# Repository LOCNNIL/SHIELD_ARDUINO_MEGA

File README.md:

# SHIELD_ARDUINO_MEGA
An Arduino Mega Shield with the purpose to be a Flight controller

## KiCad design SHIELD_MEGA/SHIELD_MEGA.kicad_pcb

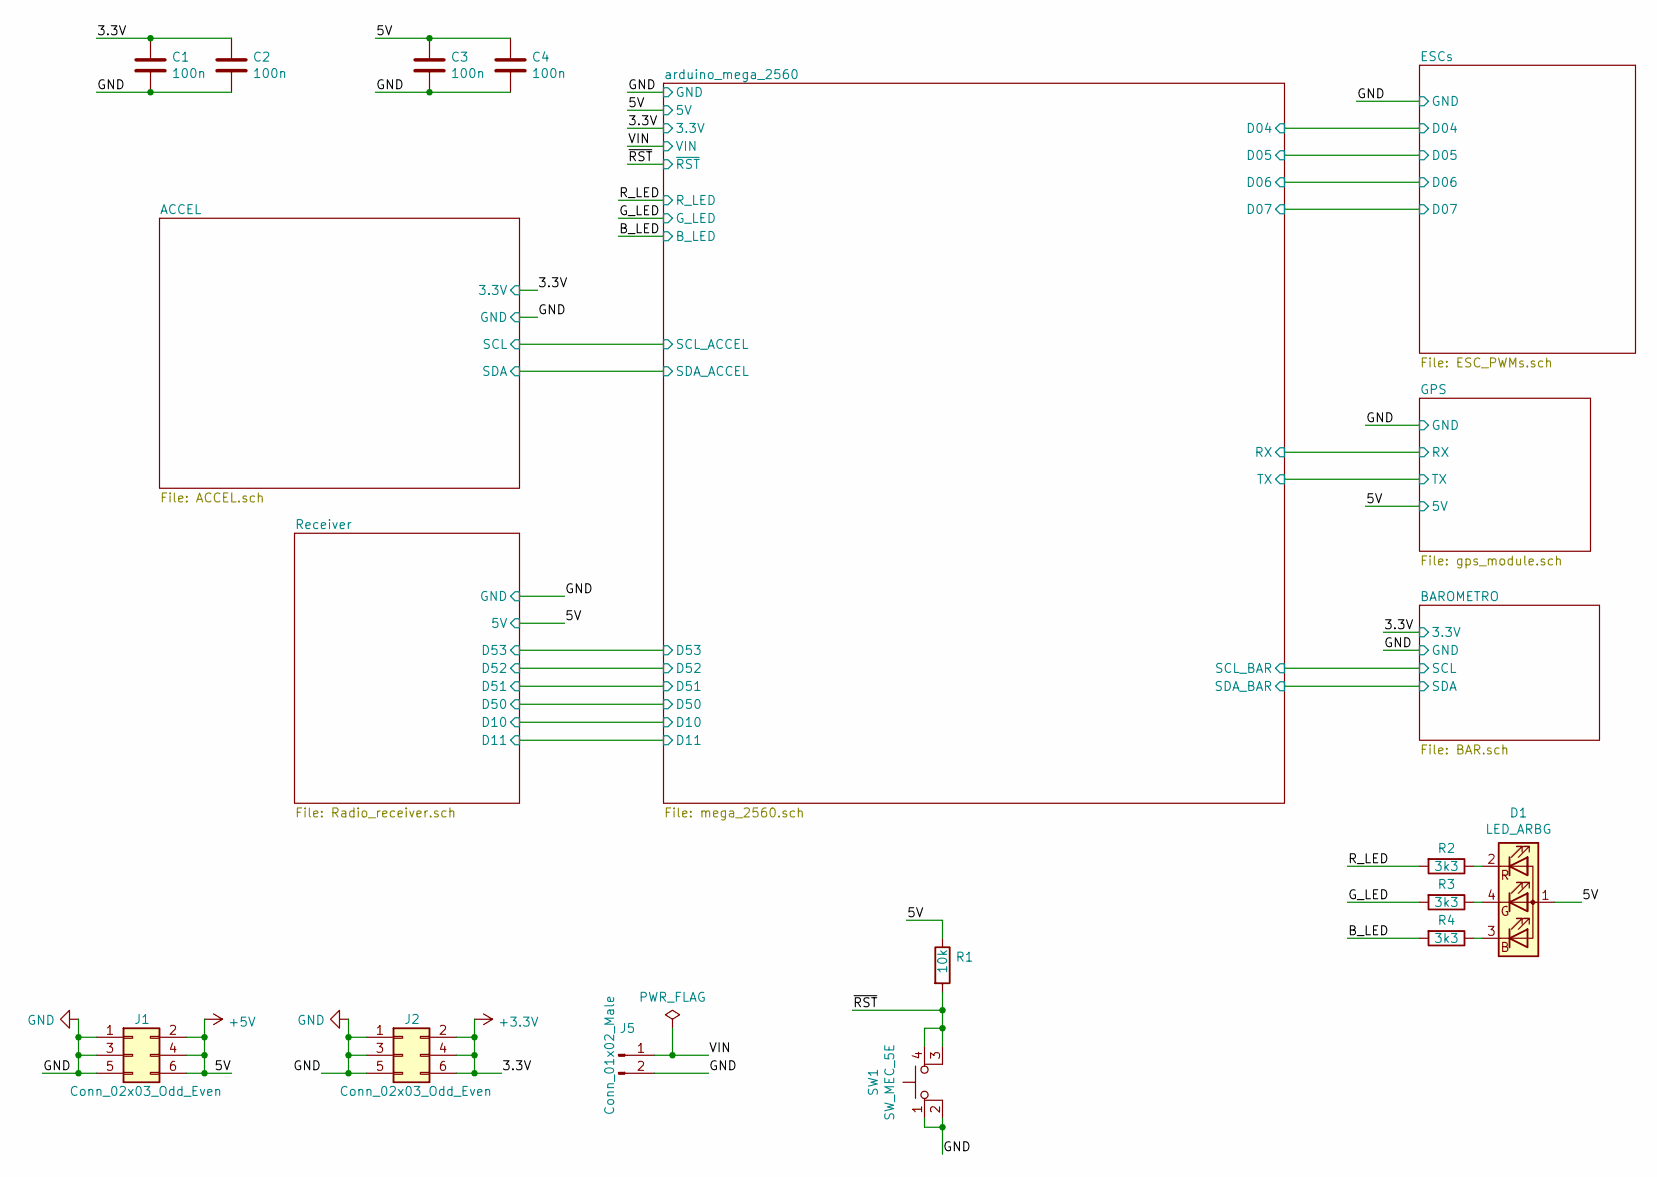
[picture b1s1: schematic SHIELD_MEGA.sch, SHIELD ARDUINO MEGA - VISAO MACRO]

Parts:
C1, C2, C3, C4: 100n; C_0805_2012Metric_Pad1.18x1.45mm_HandSolder
D1: LED_ARBG; LED_LL-R3528RGBC-008-B
J1, J2: Conn_02x03_Odd_Even; PinHeader_2x03_P2.54mm_Vertical
J5: Conn_01x02_Male; PinHeader_1x02_P2.54mm_Vertical
R1: 10k; R_0805_2012Metric_Pad1.20x1.40mm_HandSolder
R2, R3, R4: 3k3; R_0805_2012Metric_Pad1.20x1.40mm_HandSolder
SW1: SW_MEC_5E; TE_1825910-2

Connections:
+3V3: C1.1, C2.1, J2.2, J2.4, J2.6; also elsewhere on the board
+5V: C3.1, C4.1, D1.1 (A), J1.2, J1.4, J1.6, R1.1; also elsewhere on the board
/B_LED: R4.2; also elsewhere on the board
/G_LED: R3.2; also elsewhere on the board
/R_LED: R2.2; also elsewhere on the board
/VIN: J5.1; also elsewhere on the board
/~RST: R1.2, SW1.3 (K), SW1.4 (A); also elsewhere on the board
GND: C1.2, C2.2, C3.2, C4.2, J1.1, J1.3, J1.5, J2.1, J2.3, J2.5, J5.2, SW1.1, SW1.2; also elsewhere on the board
unnamed: D1.2 (RK), R2.1
unnamed: D1.3 (BK), R4.1
unnamed: D1.4 (GK), R3.1

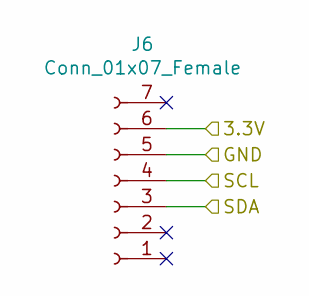
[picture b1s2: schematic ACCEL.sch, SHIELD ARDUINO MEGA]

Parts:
J6: Conn_01x07_Female; PinSocket_1x07_P2.54mm_Vertical

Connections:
+3V3: J6.6; also elsewhere on the board
/ACCEL/SCL: J6.4; also elsewhere on the board
/ACCEL/SDA: J6.3; also elsewhere on the board
GND: J6.5; also elsewhere on the board

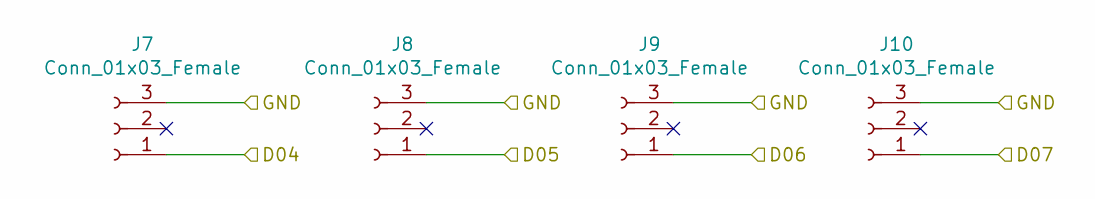
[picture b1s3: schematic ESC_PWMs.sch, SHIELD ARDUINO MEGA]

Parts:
J7, J8, J9, J10: Conn_01x03_Female; PinSocket_1x03_P2.54mm_Vertical

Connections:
/ESCs/D04: J7.1; also elsewhere on the board
/ESCs/D05: J8.1; also elsewhere on the board
/ESCs/D06: J9.1; also elsewhere on the board
/ESCs/D07: J10.1; also elsewhere on the board
GND: J7.3, J8.3, J9.3, J10.3; also elsewhere on the board

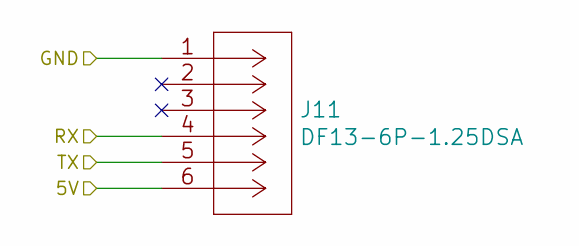
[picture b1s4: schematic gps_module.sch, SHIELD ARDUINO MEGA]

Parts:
J11: DF13-6P-1.25DSA; Hirose_DF13-06P-1.25DSA_1x06_P1.25mm_Vertical

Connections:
+5V: J11.6; also elsewhere on the board
/GPS/RX: J11.4; also elsewhere on the board
/GPS/TX: J11.5; also elsewhere on the board
GND: J11.1; also elsewhere on the board

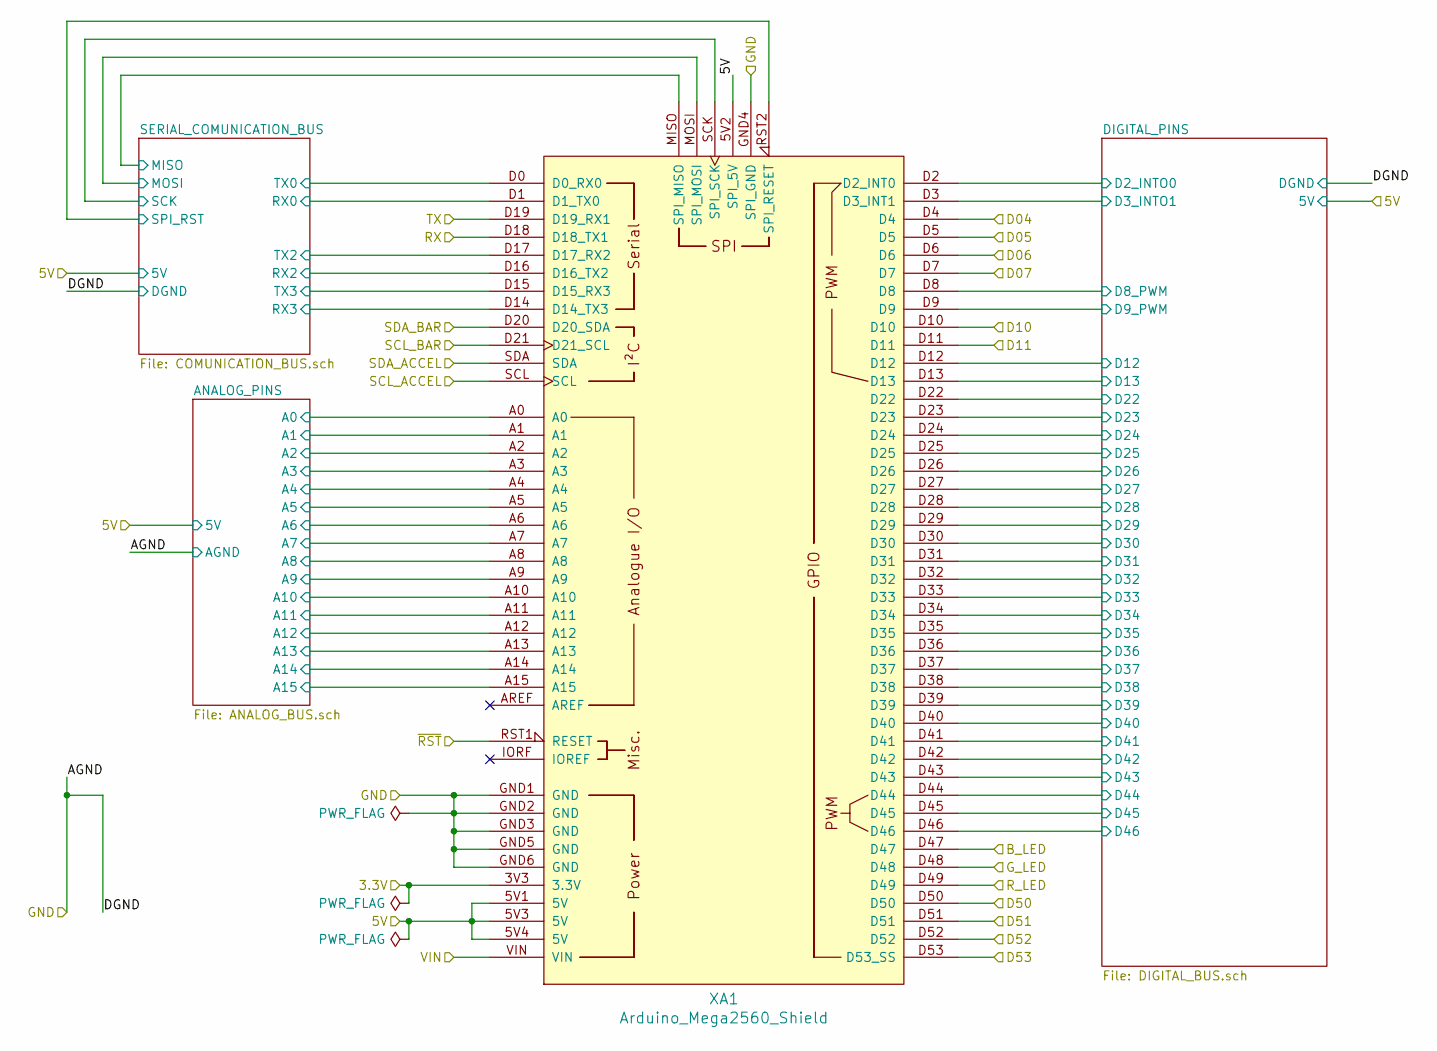
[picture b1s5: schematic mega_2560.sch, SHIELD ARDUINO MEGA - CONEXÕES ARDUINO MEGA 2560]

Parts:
XA1: Arduino_Mega2560_Shield

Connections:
+3V3: XA1.3V3 (3.3V); also elsewhere on the board
+5V: XA1.5V1 (5V), XA1.5V2 (SPI_5V), XA1.5V3 (5V), XA1.5V4 (5V); also elsewhere on the board
/ACCEL/SCL: XA1.SCL; also elsewhere on the board
/ACCEL/SDA: XA1.SDA; also elsewhere on the board
/BAROMETRO/SCL: XA1.D21 (D21_SCL); also elsewhere on the board
/BAROMETRO/SDA: XA1.D20 (D20_SDA); also elsewhere on the board
/B_LED: XA1.D47; also elsewhere on the board
/ESCs/D04: XA1.D4; also elsewhere on the board
/ESCs/D05: XA1.D5; also elsewhere on the board
/ESCs/D06: XA1.D6; also elsewhere on the board
/ESCs/D07: XA1.D7; also elsewhere on the board
/GPS/RX: XA1.D18 (D18_TX1); also elsewhere on the board
/GPS/TX: XA1.D19 (D19_RX1); also elsewhere on the board
/G_LED: XA1.D48; also elsewhere on the board
/R_LED: XA1.D49; also elsewhere on the board
/Receiver/D10: XA1.D10; also elsewhere on the board
/Receiver/D11: XA1.D11; also elsewhere on the board
/Receiver/D50: XA1.D50; also elsewhere on the board
/Receiver/D51: XA1.D51; also elsewhere on the board
/Receiver/D52: XA1.D52; also elsewhere on the board
/Receiver/D53: XA1.D53 (D53_SS); also elsewhere on the board
/VIN: XA1.VIN; also elsewhere on the board
/arduino_mega_2560/ANALOG_PINS/A0: XA1.A0; also elsewhere on the board
/arduino_mega_2560/ANALOG_PINS/A1: XA1.A1; also elsewhere on the board
/arduino_mega_2560/ANALOG_PINS/A2: XA1.A2; also elsewhere on the board
/arduino_mega_2560/ANALOG_PINS/A3: XA1.A3; also elsewhere on the board
/arduino_mega_2560/ANALOG_PINS/A4: XA1.A4; also elsewhere on the board
/arduino_mega_2560/ANALOG_PINS/A5: XA1.A5; also elsewhere on the board
/arduino_mega_2560/ANALOG_PINS/A6: XA1.A6; also elsewhere on the board
/arduino_mega_2560/ANALOG_PINS/A7: XA1.A7; also elsewhere on the board
/arduino_mega_2560/ANALOG_PINS/A8: XA1.A8; also elsewhere on the board
/arduino_mega_2560/ANALOG_PINS/A9: XA1.A9; also elsewhere on the board
/arduino_mega_2560/ANALOG_PINS/A10: XA1.A10; also elsewhere on the board
/arduino_mega_2560/ANALOG_PINS/A11: XA1.A11; also elsewhere on the board
/arduino_mega_2560/ANALOG_PINS/A12: XA1.A12; also elsewhere on the board
/arduino_mega_2560/ANALOG_PINS/A13: XA1.A13; also elsewhere on the board
/arduino_mega_2560/ANALOG_PINS/A14: XA1.A14; also elsewhere on the board
/arduino_mega_2560/ANALOG_PINS/A15: XA1.A15; also elsewhere on the board
/arduino_mega_2560/DIGITAL_PINS/D2_INTO0: XA1.D2 (D2_INT0); also elsewhere on the board
/arduino_mega_2560/DIGITAL_PINS/D3_INTO1: XA1.D3 (D3_INT1); also elsewhere on the board
/arduino_mega_2560/DIGITAL_PINS/D8_PWM: XA1.D8; also elsewhere on the board
/arduino_mega_2560/DIGITAL_PINS/D9_PWM: XA1.D9; also elsewhere on the board
/arduino_mega_2560/DIGITAL_PINS/D12: XA1.D12; also elsewhere on the board
/arduino_mega_2560/DIGITAL_PINS/D13: XA1.D13; also elsewhere on the board
/arduino_mega_2560/DIGITAL_PINS/D22: XA1.D22; also elsewhere on the board
/arduino_mega_2560/DIGITAL_PINS/D23: XA1.D23; also elsewhere on the board
/arduino_mega_2560/DIGITAL_PINS/D24: XA1.D24; also elsewhere on the board
/arduino_mega_2560/DIGITAL_PINS/D25: XA1.D25; also elsewhere on the board
/arduino_mega_2560/DIGITAL_PINS/D26: XA1.D26; also elsewhere on the board
/arduino_mega_2560/DIGITAL_PINS/D27: XA1.D27; also elsewhere on the board
/arduino_mega_2560/DIGITAL_PINS/D28: XA1.D28; also elsewhere on the board
/arduino_mega_2560/DIGITAL_PINS/D29: XA1.D29; also elsewhere on the board
/arduino_mega_2560/DIGITAL_PINS/D30: XA1.D30; also elsewhere on the board
/arduino_mega_2560/DIGITAL_PINS/D31: XA1.D31; also elsewhere on the board
/arduino_mega_2560/DIGITAL_PINS/D32: XA1.D32; also elsewhere on the board
/arduino_mega_2560/DIGITAL_PINS/D33: XA1.D33; also elsewhere on the board
/arduino_mega_2560/DIGITAL_PINS/D34: XA1.D34; also elsewhere on the board
/arduino_mega_2560/DIGITAL_PINS/D35: XA1.D35; also elsewhere on the board
/arduino_mega_2560/DIGITAL_PINS/D36: XA1.D36; also elsewhere on the board
/arduino_mega_2560/DIGITAL_PINS/D37: XA1.D37; also elsewhere on the board
/arduino_mega_2560/DIGITAL_PINS/D38: XA1.D38; also elsewhere on the board
/arduino_mega_2560/DIGITAL_PINS/D39: XA1.D39; also elsewhere on the board
/arduino_mega_2560/DIGITAL_PINS/D40: XA1.D40; also elsewhere on the board
/arduino_mega_2560/DIGITAL_PINS/D41: XA1.D41; also elsewhere on the board
/arduino_mega_2560/DIGITAL_PINS/D42: XA1.D42; also elsewhere on the board
/arduino_mega_2560/DIGITAL_PINS/D43: XA1.D43; also elsewhere on the board
/arduino_mega_2560/DIGITAL_PINS/D44: XA1.D44; also elsewhere on the board
/arduino_mega_2560/DIGITAL_PINS/D45: XA1.D45; also elsewhere on the board
/arduino_mega_2560/DIGITAL_PINS/D46: XA1.D46; also elsewhere on the board
/arduino_mega_2560/SERIAL_COMUNICATION_BUS/MISO: XA1.MISO (SPI_MISO); also elsewhere on the board
/arduino_mega_2560/SERIAL_COMUNICATION_BUS/MOSI: XA1.MOSI (SPI_MOSI); also elsewhere on the board
/arduino_mega_2560/SERIAL_COMUNICATION_BUS/RX0: XA1.D1 (D1_TX0); also elsewhere on the board
/arduino_mega_2560/SERIAL_COMUNICATION_BUS/RX2: XA1.D16 (D16_TX2); also elsewhere on the board
/arduino_mega_2560/SERIAL_COMUNICATION_BUS/RX3: XA1.D14 (D14_TX3); also elsewhere on the board
/arduino_mega_2560/SERIAL_COMUNICATION_BUS/SCK: XA1.SCK (SPI_SCK); also elsewhere on the board
/arduino_mega_2560/SERIAL_COMUNICATION_BUS/SPI_RST: XA1.RST2 (SPI_RESET); also elsewhere on the board
/arduino_mega_2560/SERIAL_COMUNICATION_BUS/TX0: XA1.D0 (D0_RX0); also elsewhere on the board
/arduino_mega_2560/SERIAL_COMUNICATION_BUS/TX2: XA1.D17 (D17_RX2); also elsewhere on the board
/arduino_mega_2560/SERIAL_COMUNICATION_BUS/TX3: XA1.D15 (D15_RX3); also elsewhere on the board
/~RST: XA1.RST1 (RESET); also elsewhere on the board
GND: XA1.GND1 (GND), XA1.GND2 (GND), XA1.GND3 (GND), XA1.GND4 (SPI_GND), XA1.GND5 (GND), XA1.GND6 (GND); also elsewhere on the board

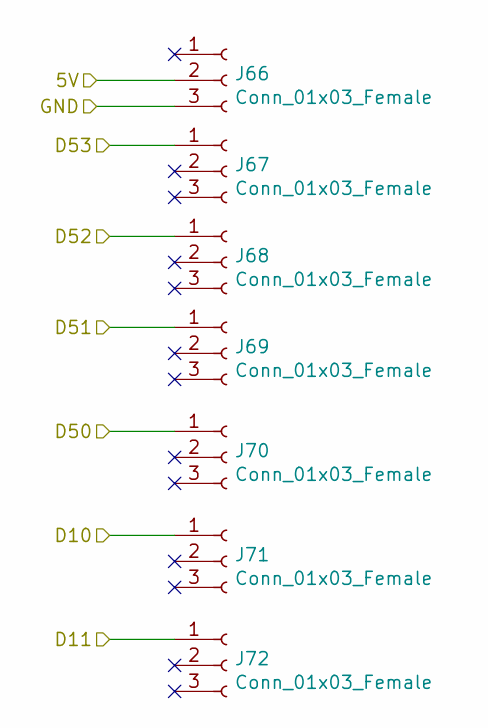
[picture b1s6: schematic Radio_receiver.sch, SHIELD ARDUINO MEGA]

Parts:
J66, J67, J68, J69, J70, J71, J72: Conn_01x03_Female; PinSocket_1x03_P2.54mm_Vertical

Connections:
+5V: J66.2; also elsewhere on the board
/Receiver/D10: J71.1; also elsewhere on the board
/Receiver/D11: J72.1; also elsewhere on the board
/Receiver/D50: J70.1; also elsewhere on the board
/Receiver/D51: J69.1; also elsewhere on the board
/Receiver/D52: J68.1; also elsewhere on the board
/Receiver/D53: J67.1; also elsewhere on the board
GND: J66.3; also elsewhere on the board

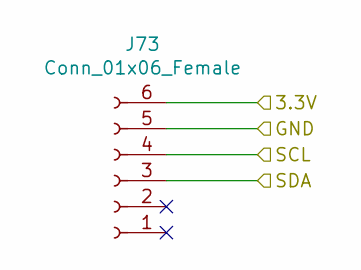
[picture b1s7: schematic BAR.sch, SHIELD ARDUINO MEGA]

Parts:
J73: Conn_01x06_Female; PinSocket_1x06_P2.54mm_Vertical

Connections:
+3V3: J73.6; also elsewhere on the board
/BAROMETRO/SCL: J73.4; also elsewhere on the board
/BAROMETRO/SDA: J73.3; also elsewhere on the board
GND: J73.5; also elsewhere on the board

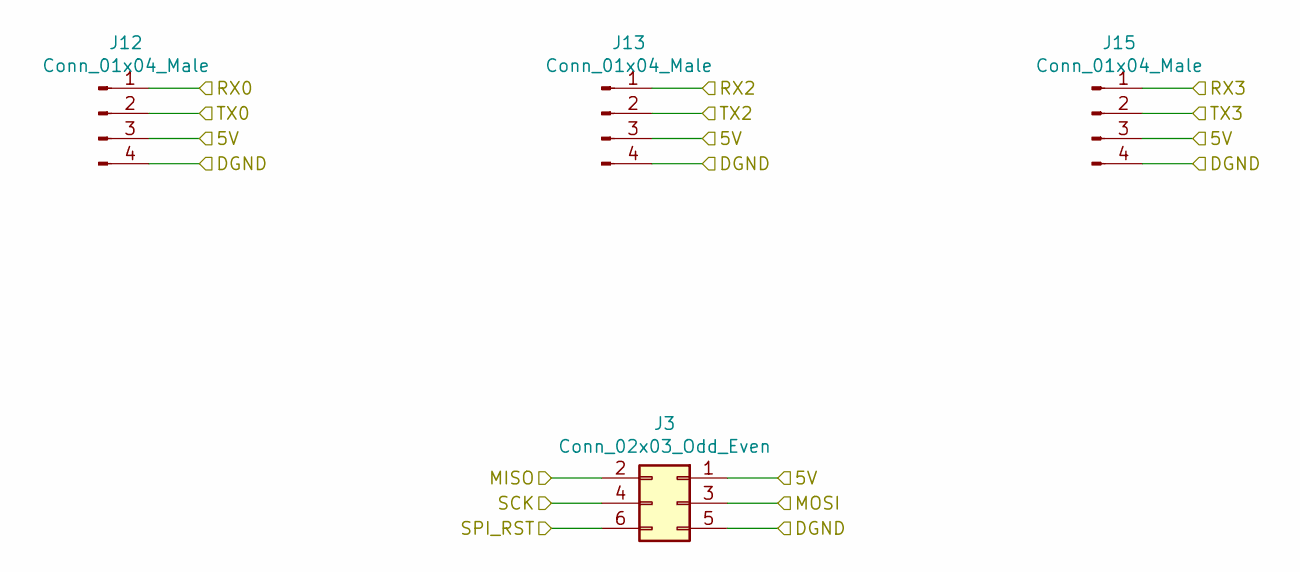
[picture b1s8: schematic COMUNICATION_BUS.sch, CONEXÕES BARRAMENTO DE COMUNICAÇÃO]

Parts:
J3: Conn_02x03_Odd_Even; PinSocket_2x03_P2.54mm_Vertical
J12, J13, J15: Conn_01x04_Male; PinHeader_1x04_P2.54mm_Vertical

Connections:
+5V: J3.1, J12.3, J13.3, J15.3; also elsewhere on the board
/arduino_mega_2560/SERIAL_COMUNICATION_BUS/MISO: J3.2; also elsewhere on the board
/arduino_mega_2560/SERIAL_COMUNICATION_BUS/MOSI: J3.3; also elsewhere on the board
/arduino_mega_2560/SERIAL_COMUNICATION_BUS/RX0: J12.1; also elsewhere on the board
/arduino_mega_2560/SERIAL_COMUNICATION_BUS/RX2: J13.1; also elsewhere on the board
/arduino_mega_2560/SERIAL_COMUNICATION_BUS/RX3: J15.1; also elsewhere on the board
/arduino_mega_2560/SERIAL_COMUNICATION_BUS/SCK: J3.4; also elsewhere on the board
/arduino_mega_2560/SERIAL_COMUNICATION_BUS/SPI_RST: J3.6; also elsewhere on the board
/arduino_mega_2560/SERIAL_COMUNICATION_BUS/TX0: J12.2; also elsewhere on the board
/arduino_mega_2560/SERIAL_COMUNICATION_BUS/TX2: J13.2; also elsewhere on the board
/arduino_mega_2560/SERIAL_COMUNICATION_BUS/TX3: J15.2; also elsewhere on the board
GND: J3.5, J12.4, J13.4, J15.4; also elsewhere on the board

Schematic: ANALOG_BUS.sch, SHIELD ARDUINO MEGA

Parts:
J16, J17, J18, J19, J20, J21, J22, J23, J24, J25, J26, J27, J28, J29, J30, J31: Conn_01x03_Male; PinHeader_1x03_P2.54mm_Vertical

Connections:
+5V: J16.2, J17.2, J18.2, J19.2, J20.2, J21.2, J22.2, J23.2, J24.2, J25.2, J26.2, J27.2, J28.2, J29.2, J30.2, J31.2; also elsewhere on the board
/arduino_mega_2560/ANALOG_PINS/A0: J16.1; also elsewhere on the board
/arduino_mega_2560/ANALOG_PINS/A1: J17.1; also elsewhere on the board
/arduino_mega_2560/ANALOG_PINS/A2: J18.1; also elsewhere on the board
/arduino_mega_2560/ANALOG_PINS/A3: J19.1; also elsewhere on the board
/arduino_mega_2560/ANALOG_PINS/A4: J20.1; also elsewhere on the board
/arduino_mega_2560/ANALOG_PINS/A5: J21.1; also elsewhere on the board
/arduino_mega_2560/ANALOG_PINS/A6: J22.1; also elsewhere on the board
/arduino_mega_2560/ANALOG_PINS/A7: J23.1; also elsewhere on the board
/arduino_mega_2560/ANALOG_PINS/A8: J24.1; also elsewhere on the board
/arduino_mega_2560/ANALOG_PINS/A9: J25.1; also elsewhere on the board
/arduino_mega_2560/ANALOG_PINS/A10: J26.1; also elsewhere on the board
/arduino_mega_2560/ANALOG_PINS/A11: J27.1; also elsewhere on the board
/arduino_mega_2560/ANALOG_PINS/A12: J28.1; also elsewhere on the board
/arduino_mega_2560/ANALOG_PINS/A13: J29.1; also elsewhere on the board
/arduino_mega_2560/ANALOG_PINS/A14: J30.1; also elsewhere on the board
/arduino_mega_2560/ANALOG_PINS/A15: J31.1; also elsewhere on the board
GND: J16.3, J17.3, J18.3, J19.3, J20.3, J21.3, J22.3, J23.3, J24.3, J25.3, J26.3, J27.3, J28.3, J29.3, J30.3, J31.3; also elsewhere on the board

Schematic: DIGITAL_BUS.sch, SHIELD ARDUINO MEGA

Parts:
J32, J33, J34, J35, J36, J37, J38, J39, J40, J41, J42, J43, J44, J45, J46, J47, J48, J49, J50, J51, J52, J53, J54, J55, J56, J57, J58, J62, J63, J64, J65: Conn_01x03_Male; PinHeader_1x03_P2.54mm_Vertical

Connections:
+5V: J32.2, J33.2, J34.2, J35.2, J36.2, J37.2, J38.2, J39.2, J40.2, J41.2, J42.2, J43.2, J44.2, J45.2, J46.2, J47.2, J48.2, J49.2, J50.2, J51.2, J52.2, J53.2, J54.2, J55.2, J56.2, J57.2, J58.2, J62.2, J63.2, J64.2, J65.2; also elsewhere on the board
/arduino_mega_2560/DIGITAL_PINS/D2_INTO0: J62.1; also elsewhere on the board
/arduino_mega_2560/DIGITAL_PINS/D3_INTO1: J63.1; also elsewhere on the board
/arduino_mega_2560/DIGITAL_PINS/D8_PWM: J64.1; also elsewhere on the board
/arduino_mega_2560/DIGITAL_PINS/D9_PWM: J65.1; also elsewhere on the board
/arduino_mega_2560/DIGITAL_PINS/D12: J32.1; also elsewhere on the board
/arduino_mega_2560/DIGITAL_PINS/D13: J33.1; also elsewhere on the board
/arduino_mega_2560/DIGITAL_PINS/D22: J34.1; also elsewhere on the board
/arduino_mega_2560/DIGITAL_PINS/D23: J35.1; also elsewhere on the board
/arduino_mega_2560/DIGITAL_PINS/D24: J36.1; also elsewhere on the board
/arduino_mega_2560/DIGITAL_PINS/D25: J37.1; also elsewhere on the board
/arduino_mega_2560/DIGITAL_PINS/D26: J38.1; also elsewhere on the board
/arduino_mega_2560/DIGITAL_PINS/D27: J39.1; also elsewhere on the board
/arduino_mega_2560/DIGITAL_PINS/D28: J40.1; also elsewhere on the board
/arduino_mega_2560/DIGITAL_PINS/D29: J41.1; also elsewhere on the board
/arduino_mega_2560/DIGITAL_PINS/D30: J42.1; also elsewhere on the board
/arduino_mega_2560/DIGITAL_PINS/D31: J43.1; also elsewhere on the board
/arduino_mega_2560/DIGITAL_PINS/D32: J44.1; also elsewhere on the board
/arduino_mega_2560/DIGITAL_PINS/D33: J45.1; also elsewhere on the board
/arduino_mega_2560/DIGITAL_PINS/D34: J46.1; also elsewhere on the board
/arduino_mega_2560/DIGITAL_PINS/D35: J47.1; also elsewhere on the board
/arduino_mega_2560/DIGITAL_PINS/D36: J48.1; also elsewhere on the board
/arduino_mega_2560/DIGITAL_PINS/D37: J49.1; also elsewhere on the board
/arduino_mega_2560/DIGITAL_PINS/D38: J50.1; also elsewhere on the board
/arduino_mega_2560/DIGITAL_PINS/D39: J51.1; also elsewhere on the board
/arduino_mega_2560/DIGITAL_PINS/D40: J52.1; also elsewhere on the board
/arduino_mega_2560/DIGITAL_PINS/D41: J53.1; also elsewhere on the board
/arduino_mega_2560/DIGITAL_PINS/D42: J54.1; also elsewhere on the board
/arduino_mega_2560/DIGITAL_PINS/D43: J55.1; also elsewhere on the board
/arduino_mega_2560/DIGITAL_PINS/D44: J56.1; also elsewhere on the board
/arduino_mega_2560/DIGITAL_PINS/D45: J57.1; also elsewhere on the board
/arduino_mega_2560/DIGITAL_PINS/D46: J58.1; also elsewhere on the board
GND: J32.3, J33.3, J34.3, J35.3, J36.3, J37.3, J38.3, J39.3, J40.3, J41.3, J42.3, J43.3, J44.3, J45.3, J46.3, J47.3, J48.3, J49.3, J50.3, J51.3, J52.3, J53.3, J54.3, J55.3, J56.3, J57.3, J58.3, J62.3, J63.3, J64.3, J65.3; also elsewhere on the board

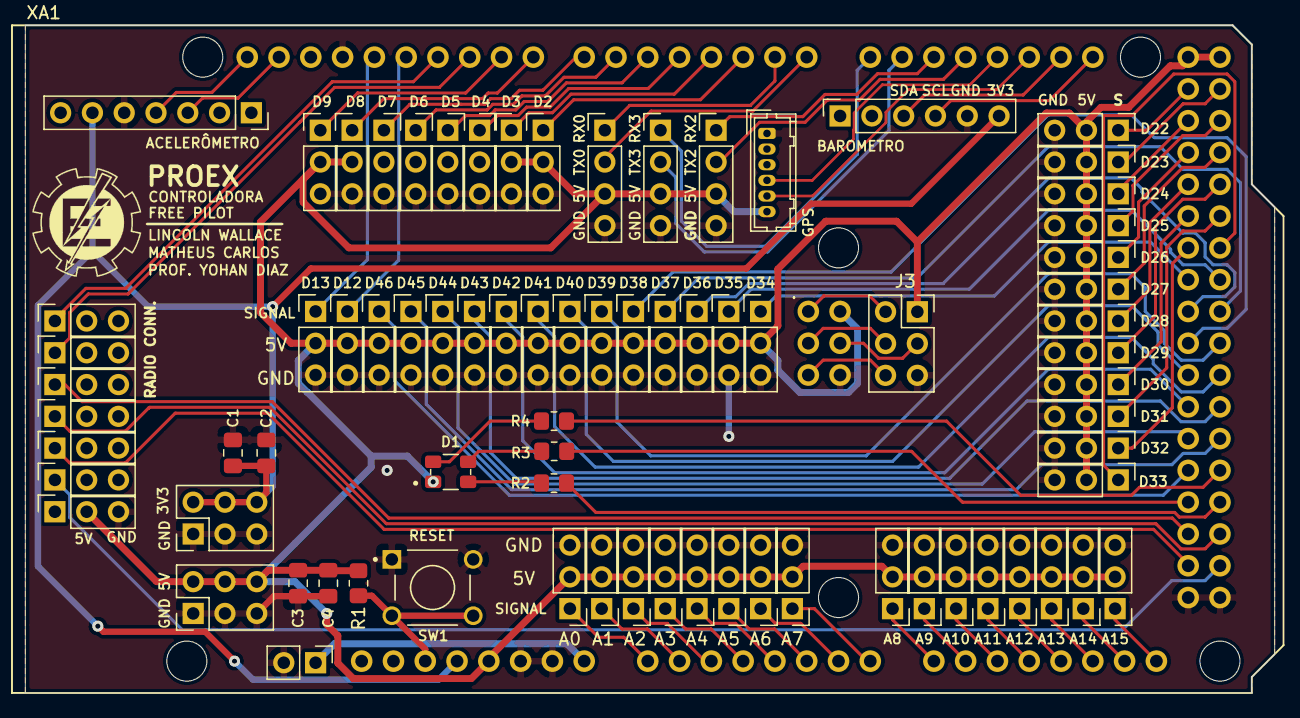
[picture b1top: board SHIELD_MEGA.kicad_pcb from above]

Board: 2 copper layers, 99.8 x 53.3 mm, 79 parts (0 on the bottom side), 84 nets.

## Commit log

2021-11-16 Adding symbol and footprint libraries
2021-11-16 First steps of schematic project
2021-11-16 Updating accel schematic
2021-11-16 Updating arduino mega sch
2021-11-16 Updating arduino mega schematic main page
2021-11-16 Adding ESC's schematic
2021-11-16 Reording pins of accel
2021-11-16 Eletronic Speed Controler Sch.
2021-11-16 Adding 2 more sch folders
2021-11-16 Radio Receiver sch
2021-11-16 GPS module sch
2021-11-16 Repositioning blocks of circuits
2021-11-18 GPS connection
2021-11-18 GND pin added to GPS
2021-11-18 GND routing
2021-11-19 Radio folder
2021-11-19 Adding new labels
2021-11-19 GPS pins position defined
2021-11-19 pins of radio receiver
2021-11-19 connectors of receiver radio
2021-11-19 Adding radio receiver bus
2021-11-19 Addings pins of receiver in mega
2021-11-19 Addings pins of receiver in mega FINISH
2021-11-19 Acelerometar sheet modification
2021-11-19 ESC_PWM sheet modification
2021-11-20 Changes in Radio sch
2021-11-20 Updating main sch
2021-11-20 Symbol of connector needs to be updated
2021-11-20 New sch to analog bus
2021-11-20 Updating
2021-11-20 New symbol and footprint lib of hirose df13-6p connector
2021-11-20 Renaming hirose symbol lib
2021-11-20 New sch to digital bus
2021-11-20 Adding sch to uart's buss
2021-11-20 Serial Comunication sch
2021-11-20 Updating lib
2021-11-20 changed sch of accel.sch
2021-11-20 Repositioning sheets
2021-11-20 fixing labels type
2021-11-20 Fixing connector symbol to be adpted for hirose df13-6p-dsa connector
2021-11-20 updating labels type
2021-11-20 library of hirose-df13-6p-dsa connector
2021-11-20 fixing label symbols type
2021-11-20 Labels in accel sheet updated
2021-11-20 Barometer sheet added
2021-11-20 Changing to female connector
2021-11-20 Changing local label to hierarch label
2021-11-20 Adding uart pins in comunication sheet
2021-11-20 Adding SPI bus
2021-11-20 Updating labels to hierarch in digital pins sheet
2021-11-20 Changing conections on receiver sheet
2021-11-20 Chaging to male connectors
2021-11-21 Repositioning connectors and changing connection order
2021-11-21 Comunication sheet done
2021-11-21 Inserting alimentation pins in digital sheet
2021-11-21 Finished digital sheet
2021-11-21 Repositioning
2021-11-21 Anotations in ACCEL sheet
2021-11-21 Defining ref number to parts
2021-11-21 Anotations in barometer sheet
2021-11-21 Defining ref number to parts in comunication sheet
2021-11-21 Anotations of ref. parts in digital sheet
2021-11-21 Anotations of ref. parts in pwm esc's sheet
2021-11-21 Anotations of ref. parts in radio receptor sheet
2021-11-21 Updating main sheet
2021-11-21 Linking symbol to footprint
2021-11-21 Updating ref's
2021-11-21 Barometer conections
2021-11-21 Linking symbols with footprints in comunication sheet
2021-11-21 Linking symbols with footprints in digital sheet
2021-11-21 Updating ref's in pwm sheet
2021-11-22 fixing footprint ref
2021-11-22 Updating sheet name
2021-11-22 Changing symbol on comunication sheet
2021-11-22 changing ref number in radio sheet
2021-11-22 Cache lib in main sheet
2021-11-22 Starting work with pcb design
2021-11-22 Changes in netlist and other
2021-11-22 Updating references in sheet
2021-11-23 Removing connectors to use in RGB led
2021-11-23 Updating cache of main lib
2021-11-23 Adding RGB led on main sheet
2021-11-23 Deleting sheet unrelated
2021-11-23 Push button and hirose df13 libraries
2021-11-23 Renaming and atribute footprint to symbol
2021-11-23 Push button footprint library
2021-11-23 Inserting RGB led to notifications
2021-11-23 Removind redudant ICSP interface
2021-11-24 Changing RGB led symbol
2021-11-24 Adding footprint to RGB led resistors
2021-11-24 hirose connector DF13
2021-11-24 Addding LED RGB footprint library
2021-11-27 Removing inductors AGND-to-DGND
2021-11-27 Updates in main file
2021-11-27 Adding UNIFEI logo library
2021-11-27 Changes in PCB
2021-11-27 Upddates in projct sheet info
2021-11-28 Removing old hirose DF-13 footprint connector
2021-11-28 Changing RGB led alimentation to 5V
2021-11-28 Roting to new alimentation of RGB LED
2021-11-28 Edge cuts
2021-11-28 Gerbers added
2021-11-28 push button 3d CAD model
2021-11-28 3d CAD's folder
2021-11-28 Hirose connector footprint
2021-11-28 RGB led footprint library
2021-11-28 hirose conn footprint lib
2021-11-28 RGB led 3D cad model
2021-11-28 Zip with gerbers
2021-11-28 UNIFEI footprint brand
2021-11-28 Atmega2560 datasheet
2021-11-28 New footprint with bigger UNIFEI logo size
2021-11-28 Insert new footprint logo in bottom silkscreen
2021-11-28 Updating gerber files
2021-11-28 Updating drill files
2021-11-28 Updating final production .zip file
